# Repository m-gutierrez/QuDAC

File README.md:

# QuDAC

***TODO
+	Update performance measurements
+	include pin-out maps
+	link to ion trap theory, for voltage requirement definitions. 
+	include BOM
+	include assembly photos

This is a 12-channel 20-bit, +/-10V (+/-20V optional) 2MSPS DAC board designed for the Quanta rack system (QuACK). The card was designed to meet the system requirements described bellow while also being simple to populate and interface with the Quanta ion trap system vacuum chamber. Since we assemble these by-hand, we desired as few components as possible while still meeting the requirements of precision experiments with trapped ions. All components should be standard and easy to source, and if possible relatively cheap. A huge exception to the cheap criterion was the use of the ad5791 DAC chip, however there is a a slightly cheaper 18-bit ad5781 which is a drop-in replacement, and a significantly cheaper 16-bit version which requires modification for the different package size.

We've tested the cards at +/-10V, and have achieved reliable update rates at 2MSPS (above the 1.33MSPS datasheet spec for ad5791). Output slew's of ~50V/us have been measured on voltage swings >1V. Noise output is DAC-code dependent, currently limited by the reference-noise (~100nV/sqrt(Hz)). Which We've improved by using an adapter reference board with heavy filtering, 3-pole 1.5Hz cut-off RC filter with capacitors in a bootstrap configuration to minimize offset errors, which reduces the white-noise level to that dominated by the DAC and output op-amp of ~10-20nV/sqrt(Hz) white noise beyond 1kHz.

## Layout 

The board contains 6-layers. This was mostly due to a panel order with other designs requiring 6 layers. The board could easily be re-drawn with 4 layers.
The current layout is 

+	layer 1 - analog signals (top)
+	layer 2 - ground plane
+	layer 3 - analog signals
+	layer 4 - power planes
+	layer 5 - ground plane
+	layer 6 - digital signals (bot)

## component choice

The components where chosen to meet the system requirements, here is a list of the key QuDAC components with a list of the relevant performance spec's.

+	AD5791: DAC, 20-bit, +/-15V supply range, NSD <10nV/sqrt(Hz), 1-2MSPS update rate
+	AD8676: op-amp, +/-15V supply range, NSD <10nV/sqrt(Hz), 10MHz GBP
+	AD8620: op-amp, +/-12V supply range, NSD <10nV/sqrt(Hz), 50MHz GBP, <1us settling to 20-bit accuracy
+	See card-buffer for description of backplane interface.

## Application aim 

Trapped ion quantum computing (TIQC) requires dozens of independently controllable voltage sources with low noise (<100nV/sqrt(Hz)), wide-output range (+/-10V) and fast update rates (>1MSPS). These sources should be extend-able while maintaining synchronized updates, and allow for asynchronous clocking. 

### Output range

In the trap for our particular experiment, Sandia's high optical access trap (HOA v2), there are 96 independent control electrodes. With a trapping height ~68micron, an electrode pitch of ~70micron and control electrodes between the RF electrodes the HOA requires voltages of ~1-4V for trapping potentials producing secular frequencies $\omega_{sec} \approx 2\pi 1MHz$. And allows for +/-20V without damage to the on-chip RF-shunting capacitors. 

### Precision

### Noise level

For room temperature traps typical electric field noise at the ion, due to yet-unknown surface effects, is around ($S_{\nu} \approx 10 \mu V /m\sqrt{Hz}$), which corresponds to an electrode-voltage noise of (~100nV/sqrt(Hz)). Electric field noise in ion traps is a major concern for high fidelity operations, as current two-qubit gate mechanisms use the ions motional state and are first order sensitive to changes in the motional state during the gate operation. In order for gate fidelities to reach error correcting thresholds of ~1e-4 control-voltage noise must be kept well bellow this value. 

### Update rates

Control potentials used in TIQC is typically a compromise between many different concerns. One such concern is that the electric field noise spectrum typical goes as ~1/f such that increasing the secular frequencies is one way to reduce the error due to motional heating of the ion. Another is trap stability and overall trapping depth, since the axial-potential can easily over-take the radial psuedo-potential and reduce the trapping depth to zero. For the trapping dimensions typical used (heights of 50-150micron) useful compromises tend to be between 1-2MHz axial secular frequencies. 

This sets the time scale how changes to control voltages will affect the ions motion, i.e. the time scale for changes to be adiabatic or diabatic. We would like voltage updates to be on the order of or faster than the characteristic ion motion, so update rates exceeding 1MSPS and slew rates >1V/MHz are necessary to meet this constraint. 

### synchronized updates and clocking
The density of the DAC's per card and the clocking rate. where chosen to meet more general back-plane specifications, which takes into account additional devices of interest, clocking speeds, types of isolation achievable over various clock speeds and bus-size. In the end, a 36-bit backplane bus allows for 12-DAC's with independent sync,clock and data lines. In addition to these 36-bits there are an additional 8-bits which by-pass the card select buffers on the backplane interface, which we connect the DAC update pin (LDAC) to allowing multiple cards to be updated simultaneously. 

# Adapters 

There are 3 adapter cards used in our setup. Which assist in converting the card channels into the experiments two DB-50 connectors. 

## Combine2Cards
The first `Combine2Cards' allows us to combine two of the QuDAC cards into a single 24 channel output. The card can be placed directly on the cards within the rack, designed for accommodate the 7HP spacing of the QuACK system. The pin-out is made such that each control voltage is routed as a twisted pair with a ground wire using standard db50 cables. 

## 24CH-2x24CH
The second card, '24CH-2x24CH', copies one 24 channel output into 2 identical pin-out 24-channel outputs. Allowing 48 DAC's to control all 96 trap control voltages. The card also has a 3rd copy for probing voltage outputs.

## filterboard
The final card, 'filterboard', takes two 24-channel inputs and routes them into a single db50-connector. The board also contains 48 7-pole (or 3-pole) coilcraft.com LC filters. In our setup, these are 7-pole 300kHz LC-filters, providing 80db suppression at 1-2MHz. This board is intended to plug directly into the vacuum chamber experiment flange, which routes 100 control signals into the trap-chip through two DB-50 connectors. One of thees boards should also be configured with the resonator-line populated. On our setup, this line consists of a hand-wound ~500nH inductor, connecting to ~20pF trap capacitance producing a ~50MHz resonant frequency, and ~300pF of matching capacitance. The RF tap, consists of a high-voltage 0.2pF capacitor and a 100pF capacitor for a ~1/500 sampling voltage gain. 

# System performance

## range, offset and non-linearity

## noise spectral density

## update rate, slew rate, tone-purity

## synchronous update, clock noise

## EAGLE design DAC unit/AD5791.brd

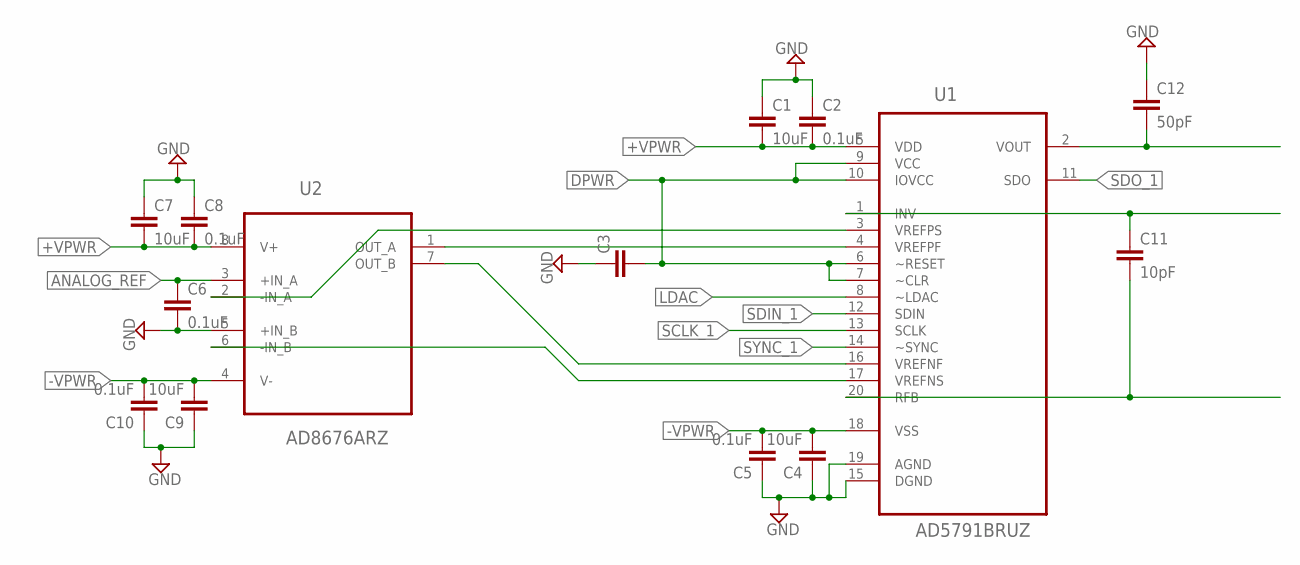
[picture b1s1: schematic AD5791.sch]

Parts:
C1, C4, C7, C9: 10uF; C0805
C2, C5, C6, C8, C10: 0.1uF; C0603
C3: CC0603; C0603
C11: 10pF; C0603
C12: 50pF; C0603
U1: AD5791BRUZ; SOP65P640X120-20N
U2: AD8676ARZ; SOIC127P600X175-8N

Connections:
+VPWR: C1.2, C2.2, C7.2, C8.2, U1.5 (VDD), U2.8 (V+)
-VPWR: C4.2, C5.2, C9.2, C10.2, U1.18 (VSS), U2.4 (V-)
ANALOG_REF: C6.1, U2.3 (+IN_A)
DPWR: C3.2, U1.6 (~RESET), U1.7 (~CLR), U1.9 (VCC), U1.10 (IOVCC)
GND: C1.1, C2.1, C3.1, C4.1, C5.1, C6.2, C7.1, C8.1, C9.1, C10.1, C12.1, U1.15 (DGND), U1.19 (AGND), U2.5 (+IN_B)
LDAC: U1.8 (~LDAC)
unnamed: U1.4 (VREFPF), U2.1 (OUT_A)
unnamed: U1.16 (VREFNF), U2.7 (OUT_B)
unnamed: U1.3 (VREFPS), U2.2 (-IN_A)
unnamed: U1.17 (VREFNS), U2.6 (-IN_B)
unnamed: C12.2, U1.2 (VOUT)
unnamed: C11.1, U1.1 (INV)
unnamed: C11.2, U1.20 (RFB)
SCLK_1: U1.13 (SCLK)
SDIN_1: U1.12 (SDIN)
SDO_1: U1.11 (SDO)
SYNC_1: U1.14 (~SYNC)

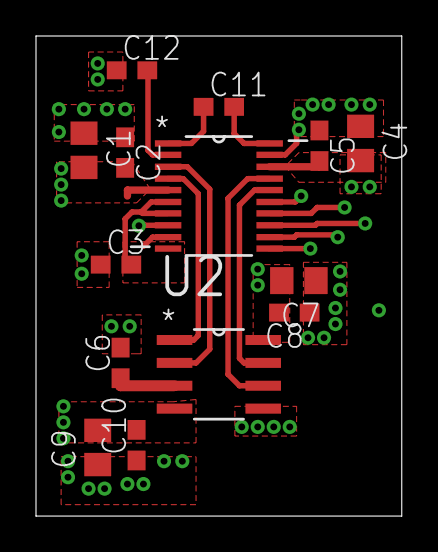
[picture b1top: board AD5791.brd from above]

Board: 4 copper layers, 20.3 x 26.7 mm, 14 parts (0 on the bottom side), 12 nets.

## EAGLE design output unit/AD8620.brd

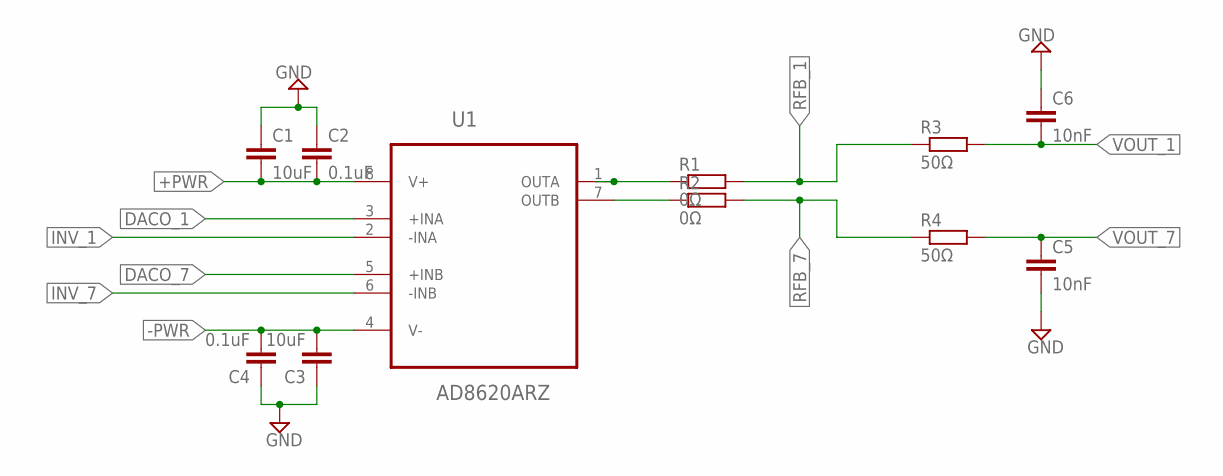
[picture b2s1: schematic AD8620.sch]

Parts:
C1, C3: 10uF; C0805
C2, C4: 0.1uF; C0603
C5, C6: 10nF; C0603
R1, R2: 0Ω; R0603
R3, R4: 50Ω; R0603
U1: AD8620ARZ; SOIC127P600X175-8N

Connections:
+PWR: C1.2, C2.2, U1.8 (V+)
-PWR: C3.2, C4.2, U1.4 (V-)
DACO_1: U1.3 (+INA)
DACO_7: U1.5 (+INB)
GND: C1.1, C2.1, C3.1, C4.1, C5.2, C6.1
INV_1: U1.2 (-INA)
INV_7: U1.6 (-INB)
unnamed: R1.1, U1.1 (OUTA)
unnamed: R2.1, U1.7 (OUTB)
RFB_1: R1.2, R3.1
RFB_7: R2.2, R4.1
VOUT_1: C6.2, R3.2
VOUT_7: C5.1, R4.2

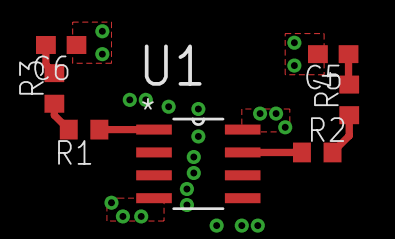
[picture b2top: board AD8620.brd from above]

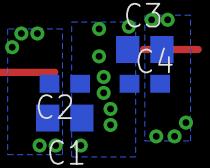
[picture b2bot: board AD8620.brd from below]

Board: 6 copper layers, 11 parts (4 on the bottom side), 9 nets.

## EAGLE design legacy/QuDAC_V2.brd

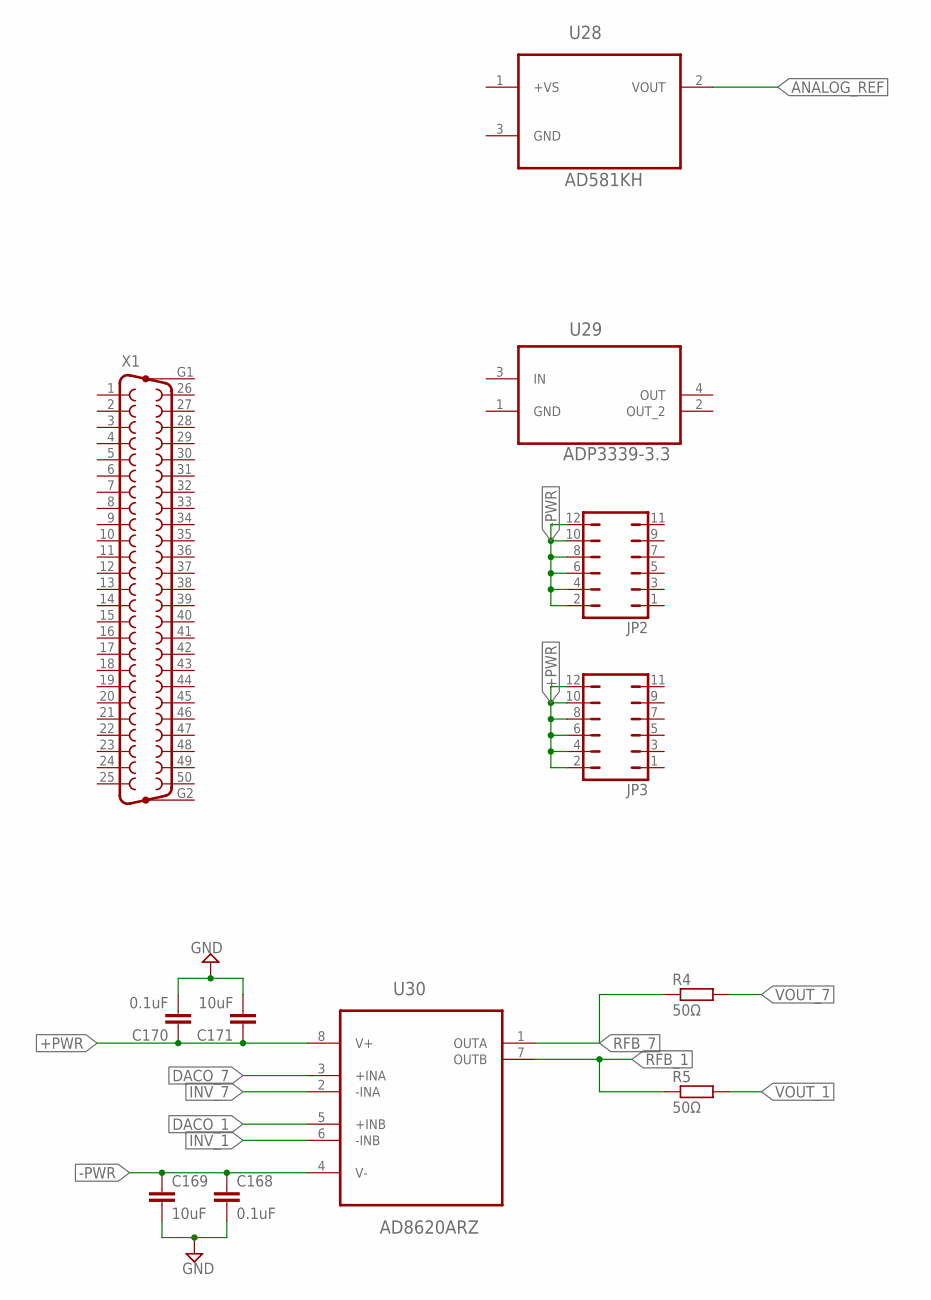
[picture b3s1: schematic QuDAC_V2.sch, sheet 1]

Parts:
C168, C170: 0.1uF; C0603
C169, C171: 10uF; C0805
JP2, JP3: JP6Q
R4, R5: 50Ω; R0603
U28: AD581KH; TO254P939X470-3P
U29: ADP3339-3.3; SOT230P700X180-4N
U30: AD8620ARZ; SOIC127P600X175-8N
X1: F50HP

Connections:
+PWR: C170.1, C171.1, JP3.2, JP3.4, JP3.6, JP3.8, JP3.10, JP3.12, U30.8 (V+)
+VS: U28.1 (+VS)
-PWR: C168.1, C169.1, JP2.2, JP2.4, JP2.6, JP2.8, JP2.10, JP2.12, U30.4 (V-)
ANALOG_REF: U28.2 (VOUT); also elsewhere on the board
DACO_1: U30.5 (+INB); also elsewhere on the board
DACO_7: U30.3 (+INA); also elsewhere on the board
GND: C168.2, C169.2, C170.2, C171.2; also elsewhere on the board
INV_1: U30.6 (-INB); also elsewhere on the board
INV_7: U30.2 (-INA); also elsewhere on the board
RFB_1: R5.1, U30.7 (OUTB); also elsewhere on the board
RFB_7: R4.1, U30.1 (OUTA); also elsewhere on the board
VOUT_1: R5.2
VOUT_7: R4.2

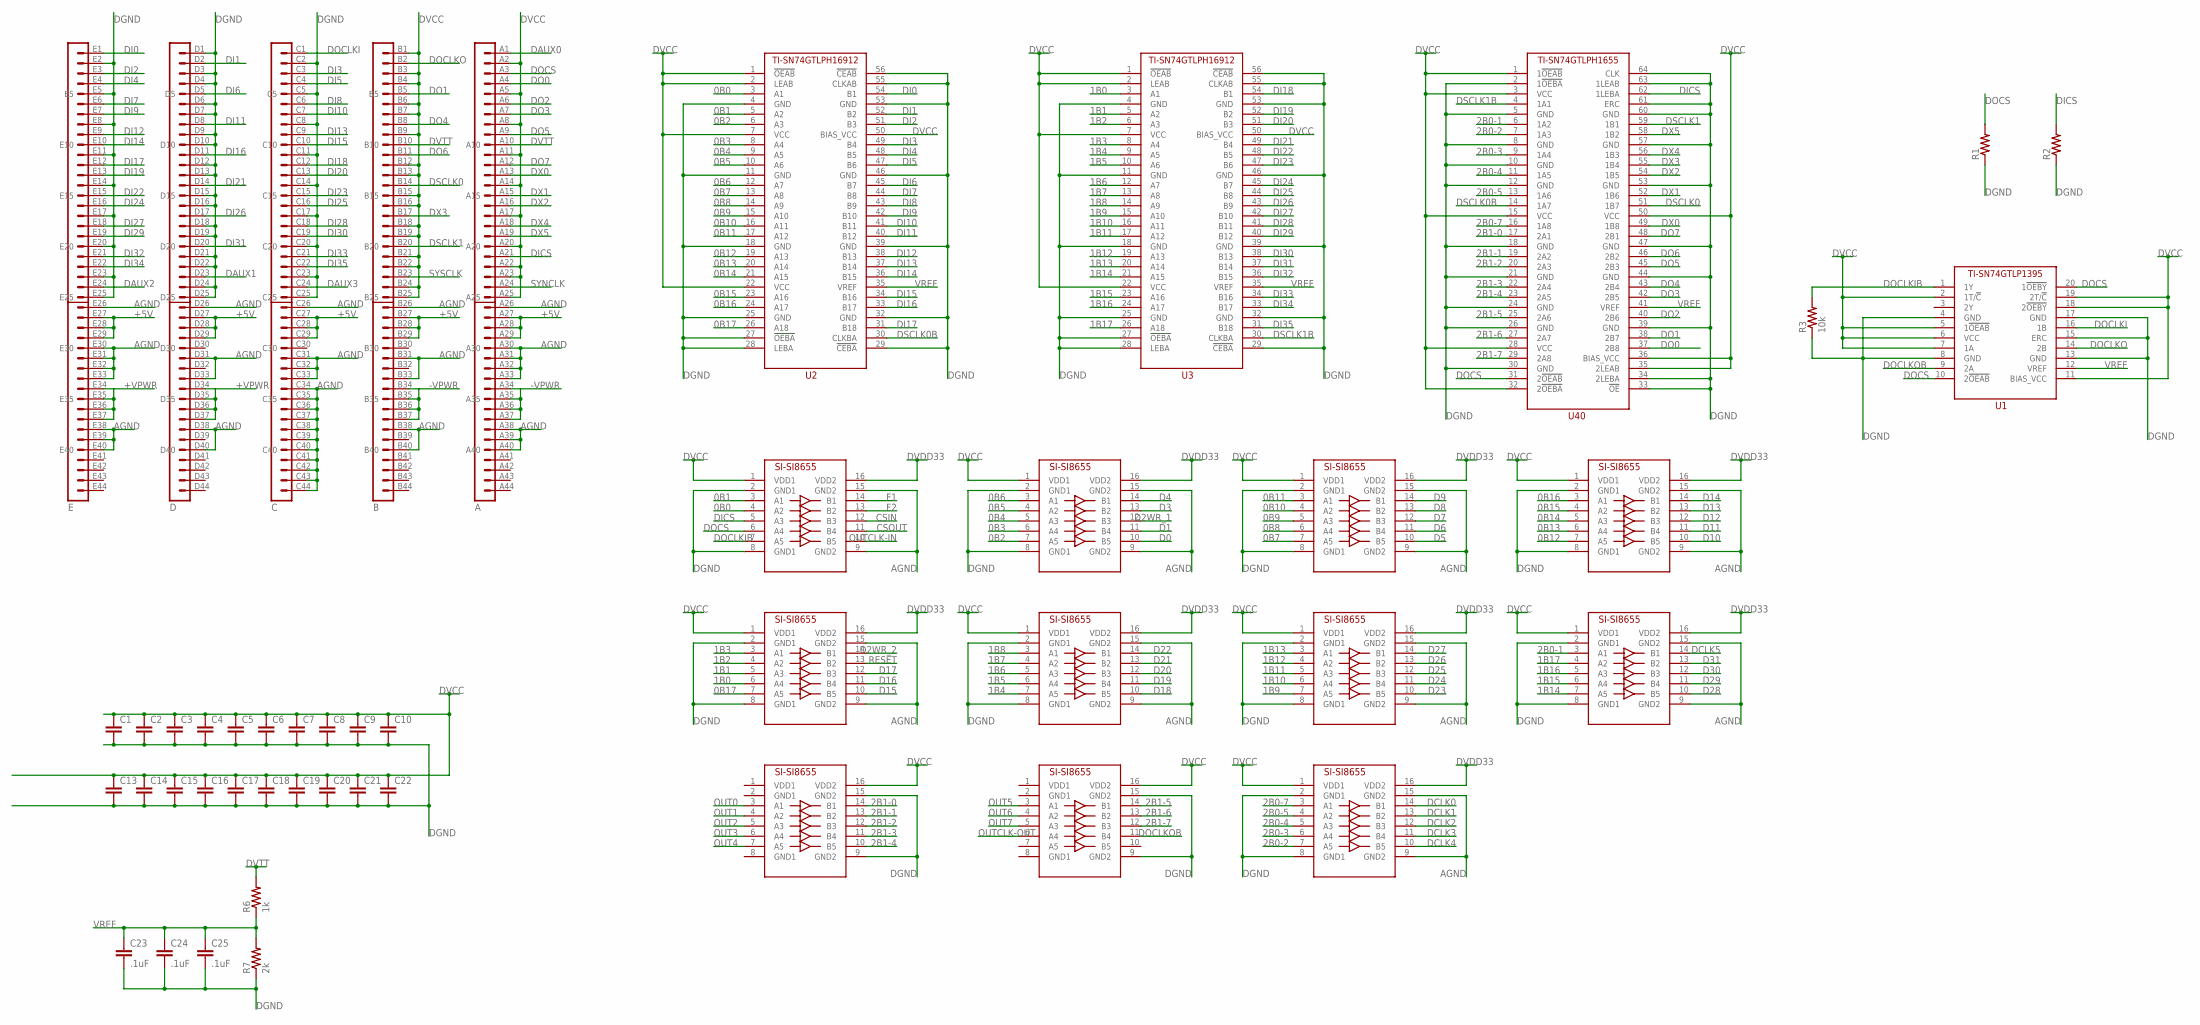
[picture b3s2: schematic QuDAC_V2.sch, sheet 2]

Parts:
C1, C2, C3, C4, C5, C6, C7, C8, C9, C10, C13, C14, C15, C16, C17, C18, C19, C20, C21, C22: CC0603; C0603
C23, C24, C25: .1uF; C0603
ISO1, ISO2, ISO3, ISO4, ISO5, ISO6, ISO7, ISO8, ISO9, ISO10, ISO11: SI-SI8655; QSOP-16
J1: EUROCARD-CPCI-220EUROCARD-B19+AB25-NOFRONTDIM; EUROCARD-CPCI-B19+1B25-NOFRONTDIM
R1, R2: R-US_R0603; R0603
R3: 10k; R0603
R6: 1k; R0805
R7: 2k; R0805
U1: TI-SN74GTLP1395; TSSOP-20
U2, U3: TI-SN74GTLPH16912; TSSOP-56
U40: TI-SN74GTLPH1655; TSSOP-64

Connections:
0B0: ISO1.4 (A2), U2.3 (A1)
0B1: ISO1.3 (A1), U2.5 (A2)
0B2: ISO2.7 (A5), U2.6 (A3)
0B3: ISO2.6 (A4), U2.8 (A4)
0B4: ISO2.5 (A3), U2.9 (A5)
0B5: ISO2.4 (A2), U2.10 (A6)
0B6: ISO2.3 (A1), U2.12 (A7)
0B7: ISO3.7 (A5), U2.13 (A8)
0B8: ISO3.6 (A4), U2.14 (A9)
0B9: ISO3.5 (A3), U2.15 (A10)
0B10: ISO3.4 (A2), U2.16 (A11)
0B11: ISO3.3 (A1), U2.17 (A12)
0B12: ISO4.7 (A5), U2.19 (A13)
0B13: ISO4.6 (A4), U2.20 (A14)
0B14: ISO4.5 (A3), U2.21 (A15)
0B15: ISO4.4 (A2), U2.23 (A16)
0B16: ISO4.3 (A1), U2.24 (A17)
0B17: ISO5.7 (A5), U2.26 (A18)
1B0: ISO5.6 (A4), U3.3 (A1)
1B1: ISO5.5 (A3), U3.5 (A2)
1B2: ISO5.4 (A2), U3.6 (A3)
1B3: ISO5.3 (A1), U3.8 (A4)
1B4: ISO6.7 (A5), U3.9 (A5)
1B5: ISO6.6 (A4), U3.10 (A6)
1B6: ISO6.5 (A3), U3.12 (A7)
1B7: ISO6.4 (A2), U3.13 (A8)
1B8: ISO6.3 (A1), U3.14 (A9)
1B9: ISO7.7 (A5), U3.15 (A10)
1B10: ISO7.6 (A4), U3.16 (A11)
1B11: ISO7.5 (A3), U3.17 (A12)
1B12: ISO7.4 (A2), U3.19 (A13)
1B13: ISO7.3 (A1), U3.20 (A14)
1B14: ISO8.7 (A5), U3.21 (A15)
1B15: ISO8.6 (A4), U3.23 (A16)
1B16: ISO8.5 (A3), U3.24 (A17)
1B17: ISO8.4 (A2), U3.26 (A18)
2B0-1: ISO8.3 (A1), U40.6 (1A2)
2B0-2: ISO11.7 (A5), U40.7 (1A3)
2B0-3: ISO11.6 (A4), U40.9 (1A4)
2B0-4: ISO11.5 (A3), U40.11 (1A5)
2B0-5: ISO11.4 (A2), U40.13 (1A6)
2B0-7: ISO11.3 (A1), U40.16 (1A8)
2B1-0: ISO9.14 (B1), U40.17 (2A1)
2B1-1: ISO9.13 (B2), U40.19 (2A2)
2B1-2: ISO9.12 (B3), U40.20 (2A3)
2B1-3: ISO9.11 (B4), U40.22 (2A4)
2B1-4: ISO9.10 (B5), U40.23 (2A5)
2B1-5: ISO10.14 (B1), U40.25 (2A6)
2B1-6: ISO10.13 (B2), U40.27 (2A7)
2B1-7: ISO10.12 (B3), U40.29 (2A8)
+5V: J1.A27, J1.A28, J1.A29, J1.B27, J1.B28, J1.B29, J1.C27, J1.C28, J1.C29, J1.D27, J1.D28, J1.D29, J1.E27, J1.E28, J1.E29
+VPWR: J1.D34, J1.D35, J1.D36, J1.D37, J1.E34, J1.E35, J1.E36, J1.E37; also elsewhere on the board
-VPWR: J1.A34, J1.A35, J1.A36, J1.A37, J1.B34, J1.B35, J1.B36, J1.B37; also elsewhere on the board
AGND: ISO1.9 (GND2), ISO1.15 (GND2), ISO2.9 (GND2), ISO2.15 (GND2), ISO3.9 (GND2), ISO3.15 (GND2), ISO4.9 (GND2), ISO4.15 (GND2), ISO5.9 (GND2), ISO5.15 (GND2), ISO6.9 (GND2), ISO6.15 (GND2), ISO7.9 (GND2), ISO7.15 (GND2), ISO8.9 (GND2), ISO8.15 (GND2), ISO11.9 (GND2), ISO11.15 (GND2), J1.A26, J1.A30, J1.A31, J1.A32, J1.A33, J1.A38, J1.A39, J1.A40, J1.B26, J1.B31, J1.B33, J1.B38, J1.B40, J1.C26, J1.C31, J1.C32, J1.C33, J1.C34, J1.C35, J1.C36, J1.C37, J1.C38, J1.C39, J1.C40, J1.C41, J1.C42, J1.C43, J1.C44, J1.D26, J1.D31, J1.D33, J1.D38, J1.D40, J1.E26, J1.E30, J1.E31, J1.E32, J1.E33, J1.E38, J1.E39, J1.E40
CSIN: ISO1.12 (B3)
CSOUT: ISO1.11 (B4)
D0: ISO2.10 (B5)
D1: ISO2.11 (B4)
D2WR_1: ISO2.12 (B3)
D2WR_2: ISO5.14 (B1)
D3: ISO2.13 (B2)
D4: ISO2.14 (B1)
D5: ISO3.10 (B5)
D6: ISO3.11 (B4)
D7: ISO3.12 (B3)
D8: ISO3.13 (B2)
D9: ISO3.14 (B1)
D10: ISO4.10 (B5)
D11: ISO4.11 (B4)
D12: ISO4.12 (B3)
D13: ISO4.13 (B2)
D14: ISO4.14 (B1)
D15: ISO5.10 (B5)
D16: ISO5.11 (B4)
D17: ISO5.12 (B3)
D18: ISO6.10 (B5)
D19: ISO6.11 (B4)
D20: ISO6.12 (B3)
D21: ISO6.13 (B2)
D22: ISO6.14 (B1)
D23: ISO7.10 (B5)
D24: ISO7.11 (B4)
D25: ISO7.12 (B3)
D26: ISO7.13 (B2)
D27: ISO7.14 (B1)
D28: ISO8.10 (B5)
D29: ISO8.11 (B4)
D30: ISO8.12 (B3)
D31: ISO8.13 (B2)
DAUX0: J1.A1
DAUX1: J1.D23
DAUX2: J1.E24
DAUX3: J1.C24
DCLK0: ISO11.14 (B1)
DCLK1: ISO11.13 (B2)
DCLK2: ISO11.12 (B3)
DCLK3: ISO11.11 (B4)
DCLK4: ISO11.10 (B5)
DCLK5: ISO8.14 (B1)
DGND: C1.2, C2.2, C3.2, C4.2, C5.2, C6.2, C7.2, C8.2, C9.2, C10.2, C13.2, C14.2, C15.2, C16.2, C17.2, C18.2, C19.2, C20.2, C21.2, C22.2, C23.2, C24.2, C25.2, ISO1.2 (GND1), ISO1.8 (GND1), ISO2.2 (GND1), ISO2.8 (GND1), ISO3.2 (GND1), ISO3.8 (GND1), ISO4.2 (GND1), ISO4.8 (GND1), ISO5.2 (GND1), ISO5.8 (GND1), ISO6.2 (GND1), ISO6.8 (GND1), ISO7.2 (GND1), ISO7.8 (GND1), ISO8.2 (GND1), ISO8.8 (GND1), ISO9.9 (GND2), ISO9.15 (GND2), ISO10.9 (GND2), ISO10.15 (GND2), ISO11.2 (GND1), ISO11.8 (GND1), J1.C2, J1.C5, J1.C8, J1.C11, J1.C14, J1.C17, J1.C20, J1.C23, J1.C25, J1.D1, J1.D3, J1.D4, J1.D6, J1.D7, J1.D9, J1.D10, J1.D12, J1.D13, J1.D15, J1.D16, J1.D18, J1.D19, J1.D21, J1.D22, J1.D24, J1.D25, J1.E2, J1.E5, J1.E8, J1.E11, J1.E14, J1.E17, J1.E20, J1.E23, J1.E25, R1.1, R2.1, R3.1, R7.1, U1.4 (GND), U1.8 (GND), U1.13 (GND), U1.15 (ERC), U1.17 (GND), U2.4 (GND), U2.11 (GND), U2.18 (GND), U2.25 (GND), U2.27 (!OEBA), U2.28 (LEBA), U2.29 (!CEBA), U2.32 (GND), U2.39 (GND), U2.46 (GND), U2.53 (GND), U2.55 (CLKAB), U2.56 (!CEAB), U3.4 (GND), U3.11 (GND), U3.18 (GND), U3.25 (GND), U3.27 (!OEBA), U3.28 (LEBA), U3.29 (!CEBA), U3.32 (GND), U3.39 (GND), U3.46 (GND), U3.53 (GND), U3.55 (CLKAB), U3.56 (!CEAB), U40.2 (1!OEBA), U40.5 (GND), U40.8 (GND), U40.10 (GND), U40.12 (GND), U40.18 (GND), U40.21 (GND), U40.24 (GND), U40.26 (GND), U40.30 (GND), U40.33 (!OE), U40.34 (2LEBA), U40.39 (GND), U40.44 (GND), U40.47 (GND), U40.53 (GND), U40.57 (GND), U40.60 (GND), U40.61 (ERC), U40.63 (1LEAB), U40.64 (CLK)
DI0: J1.E1, U2.54 (B1)
DI1: J1.D2, U2.52 (B2)
DI2: J1.E3, U2.51 (B3)
DI3: J1.C3, U2.49 (B4)
DI4: J1.E4, U2.48 (B5)
DI5: J1.C4, U2.47 (B6)
DI6: J1.D5, U2.45 (B7)
DI7: J1.E6, U2.44 (B8)
DI8: J1.C6, U2.43 (B9)
DI9: J1.E7, U2.42 (B10)
DI10: J1.C7, U2.41 (B11)
DI11: J1.D8, U2.40 (B12)
DI12: J1.E9, U2.38 (B13)
DI13: J1.C9, U2.37 (B14)
DI14: J1.E10, U2.36 (B15)
DI15: J1.C10, U2.34 (B16)
DI16: J1.D11, U2.33 (B17)
DI17: J1.E12, U2.31 (B18)
DI18: J1.C12, U3.54 (B1)
DI19: J1.E13, U3.52 (B2)
DI20: J1.C13, U3.51 (B3)
DI21: J1.D14, U3.49 (B4)
DI22: J1.E15, U3.48 (B5)
DI23: J1.C15, U3.47 (B6)
DI24: J1.E16, U3.45 (B7)
DI25: J1.C16, U3.44 (B8)
DI26: J1.D17, U3.43 (B9)
DI27: J1.E18, U3.42 (B10)
DI28: J1.C18, U3.41 (B11)
DI29: J1.E19, U3.40 (B12)
DI30: J1.C19, U3.38 (B13)
DI31: J1.D20, U3.37 (B14)
DI32: J1.E21, U3.36 (B15)
DI33: J1.C21, U3.34 (B16)
DI34: J1.E22, U3.33 (B17)
DI35: J1.C22, U3.31 (B18)
DICS: ISO1.5 (A3), J1.A21, R2.2, U40.62 (1LEBA)
DO0: J1.A4, U40.37 (2B8)
DO1: J1.B5, U40.38 (2B7)
DO2: J1.A6, U40.40 (2B6)
DO3: J1.A7, U40.42 (2B5)
DO4: J1.B8, U40.43 (2B4)
DO5: J1.A9, U40.45 (2B3)
DO6: J1.B11, U40.46 (2B2)
DO7: J1.A12, U40.48 (2B1)
DOCLKI: J1.C1, U1.16 (1B)
DOCLKIB: ISO1.7 (A5), R3.2, U1.1 (1Y)
DOCLKO: J1.B2, U1.14 (2B)
DOCLKOB: ISO10.11 (B4), U1.9 (2A)
DOCS: ISO1.6 (A4), J1.A3, R1.2, U1.10 (2!OEAB), U1.20 (1!OEBY), U40.31 (2!OEAB)
DSCLK0: J1.B14, U40.51 (1B7)
DSCLK0B: U2.30 (CLKBA), U40.14 (1A7)
DSCLK1: J1.B20, U40.59 (1B1)
DSCLK1B: U3.30 (CLKBA), U40.4 (1A1)
DVCC: C1.1, C2.1, C3.1, C4.1, C5.1, C6.1, C7.1, C8.1, C9.1, C10.1, C13.1, C14.1, C15.1, C16.1, C17.1, C18.1, C19.1, C20.1, C21.1, C22.1, ISO1.1 (VDD1), ISO2.1 (VDD1), ISO3.1 (VDD1), ISO4.1 (VDD1), ISO5.1 (VDD1), ISO6.1 (VDD1), ISO7.1 (VDD1), ISO8.1 (VDD1), ISO9.16 (VDD2), ISO10.16 (VDD2), ISO11.1 (VDD1), J1.A2, J1.A5, J1.A8, J1.A11, J1.A14, J1.A17, J1.A20, J1.A22, J1.A23, J1.A25, J1.B1, J1.B3, J1.B4, J1.B6, J1.B7, J1.B9, J1.B12, J1.B13, J1.B15, J1.B16, J1.B18, J1.B19, J1.B21, J1.B22, J1.B24, J1.B25, U1.2 (1T/!C), U1.5 (1!OEAB), U1.6 (VCC), U1.7 (1A), U1.11 (BIAS_VCC), U1.18 (2!OEBY), U1.19 (2T/!C), U2.1 (!OEAB), U2.2 (LEAB), U2.7 (VCC), U2.22 (VCC), U2.50 (BIAS_VCC), U3.1 (!OEAB), U3.2 (LEAB), U3.7 (VCC), U3.22 (VCC), U3.50 (BIAS_VCC), U40.1 (1!OEAB), U40.3 (VCC), U40.15 (VCC), U40.28 (VCC), U40.32 (2!OEBA), U40.35 (2LEAB), U40.36 (BIAS_VCC), U40.50 (VCC)
DVDD33: ISO1.16 (VDD2), ISO2.16 (VDD2), ISO3.16 (VDD2), ISO4.16 (VDD2), ISO5.16 (VDD2), ISO6.16 (VDD2), ISO7.16 (VDD2), ISO8.16 (VDD2), ISO11.16 (VDD2)
DVTT: J1.A10, J1.B10, R6.2
DX0: J1.A13, U40.49 (1B8)
DX1: J1.A15, U40.52 (1B6)
DX2: J1.A16, U40.54 (1B5)
DX3: J1.B17, U40.55 (1B4)
DX4: J1.A18, U40.56 (1B3)
DX5: J1.A19, U40.58 (1B2)
F1: ISO1.14 (B1)
F2: ISO1.13 (B2)
OUT0: ISO9.3 (A1)
OUT1: ISO9.4 (A2)
OUT2: ISO9.5 (A3)
OUT3: ISO9.6 (A4)
OUT4: ISO9.7 (A5)
OUT5: ISO10.3 (A1)
OUT6: ISO10.4 (A2)
OUT7: ISO10.5 (A3)
OUTCLK-IN: ISO1.10 (B5)
OUTCLK-OUT: ISO10.6 (A4)
RESET: ISO5.13 (B2)
SYNCLK: J1.A24
SYSCLK: J1.B23
VREF: C23.1, C24.1, C25.1, R6.1, R7.2, U1.12 (VREF), U2.35 (VREF), U3.35 (VREF), U40.41 (VREF)

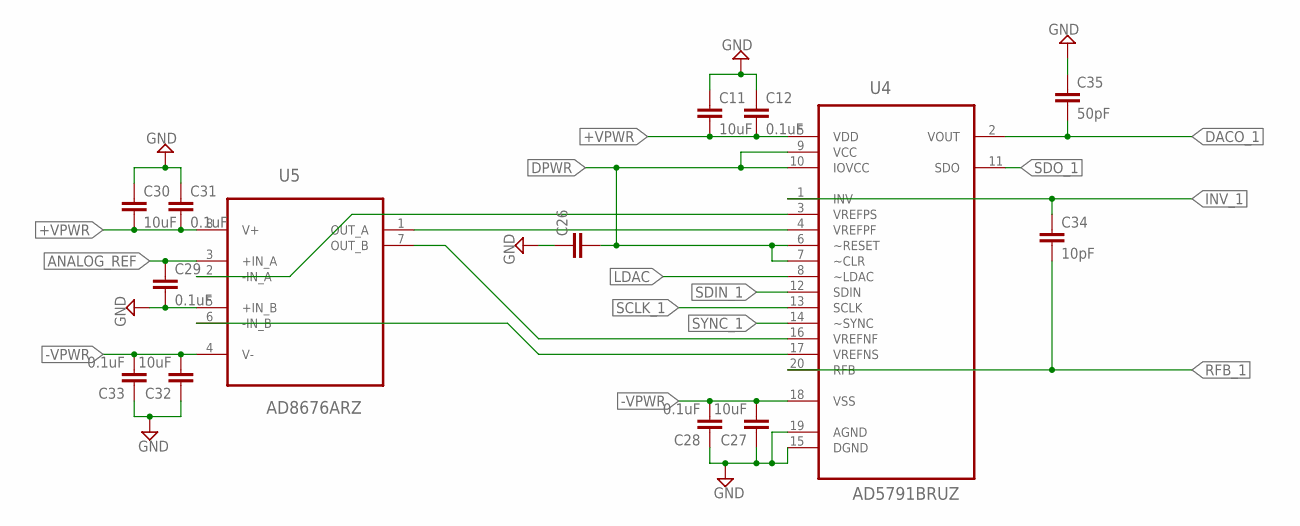
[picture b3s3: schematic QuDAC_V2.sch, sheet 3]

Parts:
C11, C27, C30, C32: 10uF; C0805
C12, C28, C29, C31, C33: 0.1uF; C0603
C26: CC0603; C0603
C34: 10pF; C0603
C35: 50pF; C0603
U4: AD5791BRUZ; SOP65P640X120-20N
U5: AD8676ARZ; SOIC127P600X175-8N

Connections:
+VPWR: C11.2, C12.2, C30.2, C31.2, U4.5 (VDD), U5.8 (V+); also elsewhere on the board
-VPWR: C27.2, C28.2, C32.2, C33.2, U4.18 (VSS), U5.4 (V-); also elsewhere on the board
ANALOG_REF: C29.1, U5.3 (+IN_A); also elsewhere on the board
DACO_1: C35.2, U4.2 (VOUT); also elsewhere on the board
DPWR: C26.2, U4.6 (~RESET), U4.7 (~CLR), U4.9 (VCC), U4.10 (IOVCC); also elsewhere on the board
GND: C11.1, C12.1, C26.1, C27.1, C28.1, C29.2, C30.1, C31.1, C32.1, C33.1, C35.1, U4.15 (DGND), U4.19 (AGND), U5.5 (+IN_B); also elsewhere on the board
INV_1: C34.1, U4.1 (INV); also elsewhere on the board
LDAC: U4.8 (~LDAC); also elsewhere on the board
unnamed: U4.4 (VREFPF), U5.1 (OUT_A)
unnamed: U4.16 (VREFNF), U5.7 (OUT_B)
unnamed: U4.3 (VREFPS), U5.2 (-IN_A)
unnamed: U4.17 (VREFNS), U5.6 (-IN_B)
RFB_1: C34.2, U4.20 (RFB); also elsewhere on the board
SCLK_1: U4.13 (SCLK)
SDIN_1: U4.12 (SDIN)
SDO_1: U4.11 (SDO)
SYNC_1: U4.14 (~SYNC)

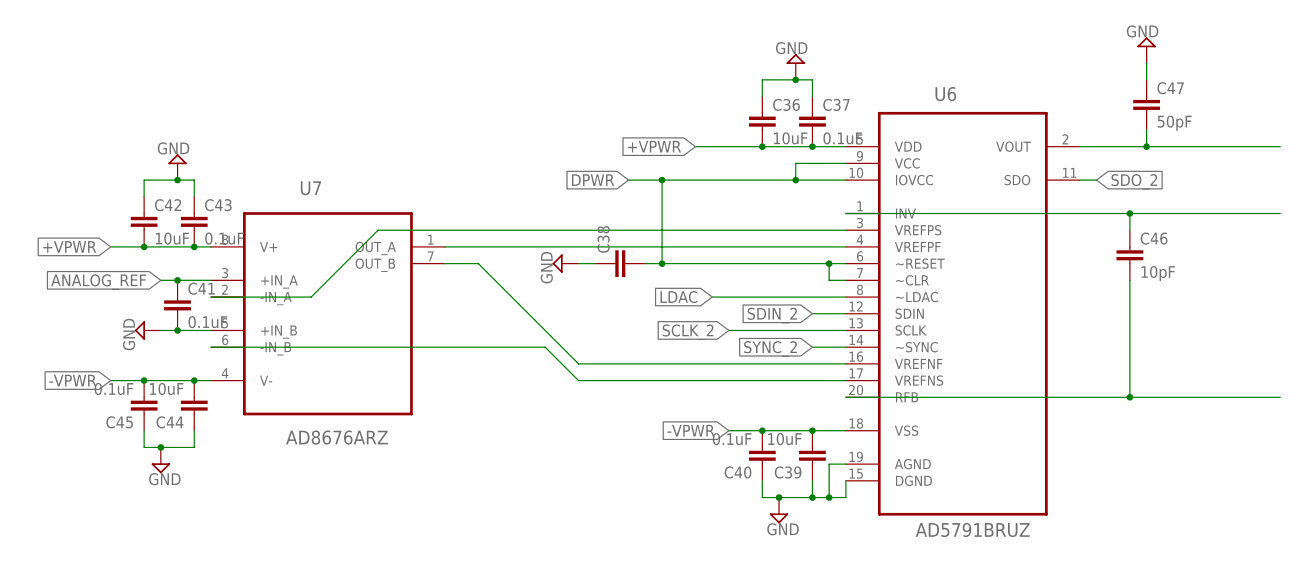
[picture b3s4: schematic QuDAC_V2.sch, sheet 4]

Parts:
C36, C39, C42, C44: 10uF; C0805
C37, C40, C41, C43, C45: 0.1uF; C0603
C38: CC0603; C0603
C46: 10pF; C0603
C47: 50pF; C0603
U6: AD5791BRUZ; SOP65P640X120-20N
U7: AD8676ARZ; SOIC127P600X175-8N

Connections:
+VPWR: C36.2, C37.2, C42.2, C43.2, U6.5 (VDD), U7.8 (V+); also elsewhere on the board
-VPWR: C39.2, C40.2, C44.2, C45.2, U6.18 (VSS), U7.4 (V-); also elsewhere on the board
ANALOG_REF: C41.1, U7.3 (+IN_A); also elsewhere on the board
DPWR: C38.2, U6.6 (~RESET), U6.7 (~CLR), U6.9 (VCC), U6.10 (IOVCC); also elsewhere on the board
GND: C36.1, C37.1, C38.1, C39.1, C40.1, C41.2, C42.1, C43.1, C44.1, C45.1, C47.1, U6.15 (DGND), U6.19 (AGND), U7.5 (+IN_B); also elsewhere on the board
LDAC: U6.8 (~LDAC); also elsewhere on the board
unnamed: U6.4 (VREFPF), U7.1 (OUT_A)
unnamed: U6.16 (VREFNF), U7.7 (OUT_B)
unnamed: U6.3 (VREFPS), U7.2 (-IN_A)
unnamed: U6.17 (VREFNS), U7.6 (-IN_B)
unnamed: C47.2, U6.2 (VOUT)
unnamed: C46.1, U6.1 (INV)
unnamed: C46.2, U6.20 (RFB)
SCLK_2: U6.13 (SCLK)
SDIN_2: U6.12 (SDIN)
SDO_2: U6.11 (SDO)
SYNC_2: U6.14 (~SYNC)

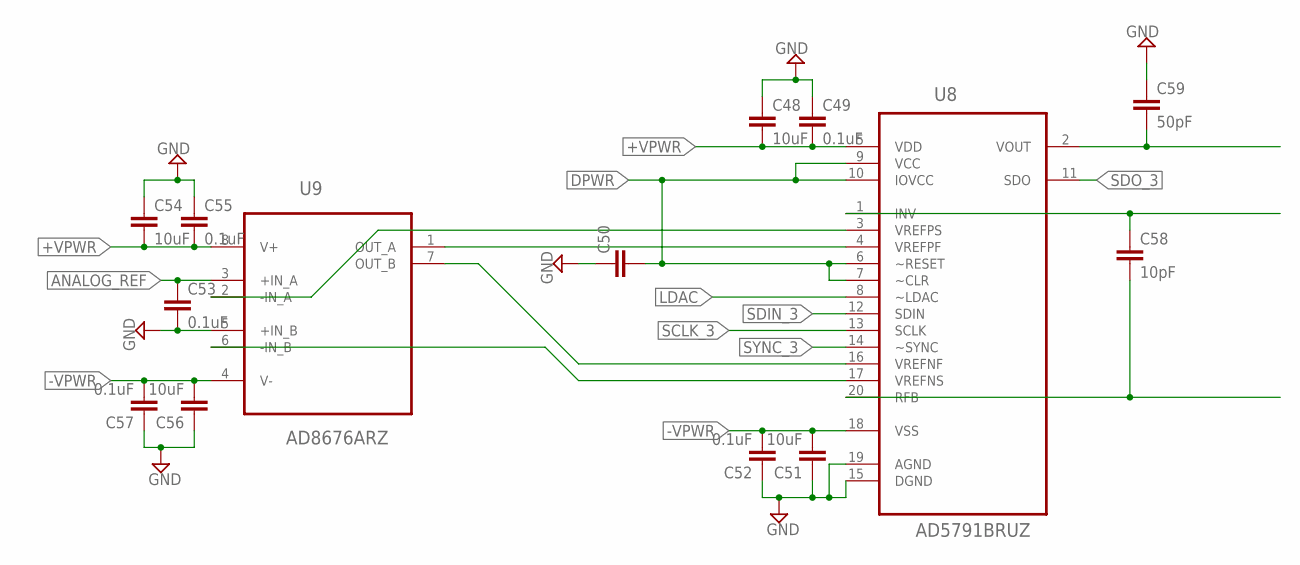
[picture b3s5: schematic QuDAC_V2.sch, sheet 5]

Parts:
C48, C51, C54, C56: 10uF; C0805
C49, C52, C53, C55, C57: 0.1uF; C0603
C50: CC0603; C0603
C58: 10pF; C0603
C59: 50pF; C0603
U8: AD5791BRUZ; SOP65P640X120-20N
U9: AD8676ARZ; SOIC127P600X175-8N

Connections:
+VPWR: C48.2, C49.2, C54.2, C55.2, U8.5 (VDD), U9.8 (V+); also elsewhere on the board
-VPWR: C51.2, C52.2, C56.2, C57.2, U8.18 (VSS), U9.4 (V-); also elsewhere on the board
ANALOG_REF: C53.1, U9.3 (+IN_A); also elsewhere on the board
DPWR: C50.2, U8.6 (~RESET), U8.7 (~CLR), U8.9 (VCC), U8.10 (IOVCC); also elsewhere on the board
GND: C48.1, C49.1, C50.1, C51.1, C52.1, C53.2, C54.1, C55.1, C56.1, C57.1, C59.1, U8.15 (DGND), U8.19 (AGND), U9.5 (+IN_B); also elsewhere on the board
LDAC: U8.8 (~LDAC); also elsewhere on the board
unnamed: U8.4 (VREFPF), U9.1 (OUT_A)
unnamed: U8.16 (VREFNF), U9.7 (OUT_B)
unnamed: U8.3 (VREFPS), U9.2 (-IN_A)
unnamed: U8.17 (VREFNS), U9.6 (-IN_B)
unnamed: C59.2, U8.2 (VOUT)
unnamed: C58.1, U8.1 (INV)
unnamed: C58.2, U8.20 (RFB)
SCLK_3: U8.13 (SCLK)
SDIN_3: U8.12 (SDIN)
SDO_3: U8.11 (SDO)
SYNC_3: U8.14 (~SYNC)

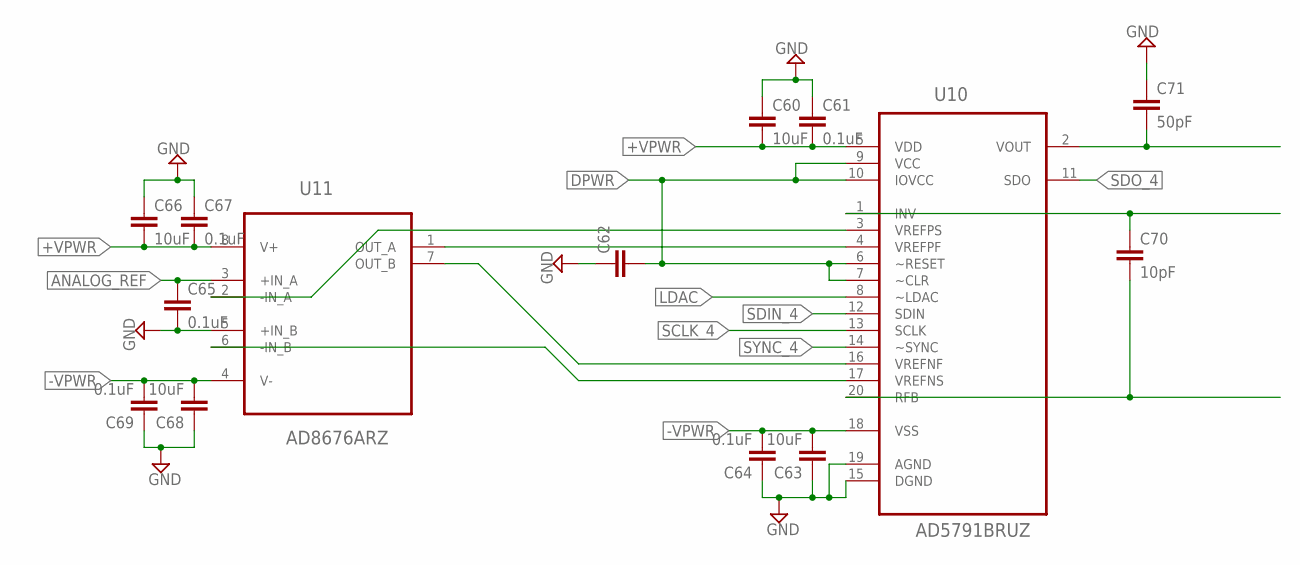
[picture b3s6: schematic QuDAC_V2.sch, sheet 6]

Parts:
C60, C63, C66, C68: 10uF; C0805
C61, C64, C65, C67, C69: 0.1uF; C0603
C62: CC0603; C0603
C70: 10pF; C0603
C71: 50pF; C0603
U10: AD5791BRUZ; SOP65P640X120-20N
U11: AD8676ARZ; SOIC127P600X175-8N

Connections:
+VPWR: C60.2, C61.2, C66.2, C67.2, U10.5 (VDD), U11.8 (V+); also elsewhere on the board
-VPWR: C63.2, C64.2, C68.2, C69.2, U10.18 (VSS), U11.4 (V-); also elsewhere on the board
ANALOG_REF: C65.1, U11.3 (+IN_A); also elsewhere on the board
DPWR: C62.2, U10.6 (~RESET), U10.7 (~CLR), U10.9 (VCC), U10.10 (IOVCC); also elsewhere on the board
GND: C60.1, C61.1, C62.1, C63.1, C64.1, C65.2, C66.1, C67.1, C68.1, C69.1, C71.1, U10.15 (DGND), U10.19 (AGND), U11.5 (+IN_B); also elsewhere on the board
LDAC: U10.8 (~LDAC); also elsewhere on the board
unnamed: U10.4 (VREFPF), U11.1 (OUT_A)
unnamed: U10.16 (VREFNF), U11.7 (OUT_B)
unnamed: U10.3 (VREFPS), U11.2 (-IN_A)
unnamed: U10.17 (VREFNS), U11.6 (-IN_B)
unnamed: C71.2, U10.2 (VOUT)
unnamed: C70.1, U10.1 (INV)
unnamed: C70.2, U10.20 (RFB)
SCLK_4: U10.13 (SCLK)
SDIN_4: U10.12 (SDIN)
SDO_4: U10.11 (SDO)
SYNC_4: U10.14 (~SYNC)

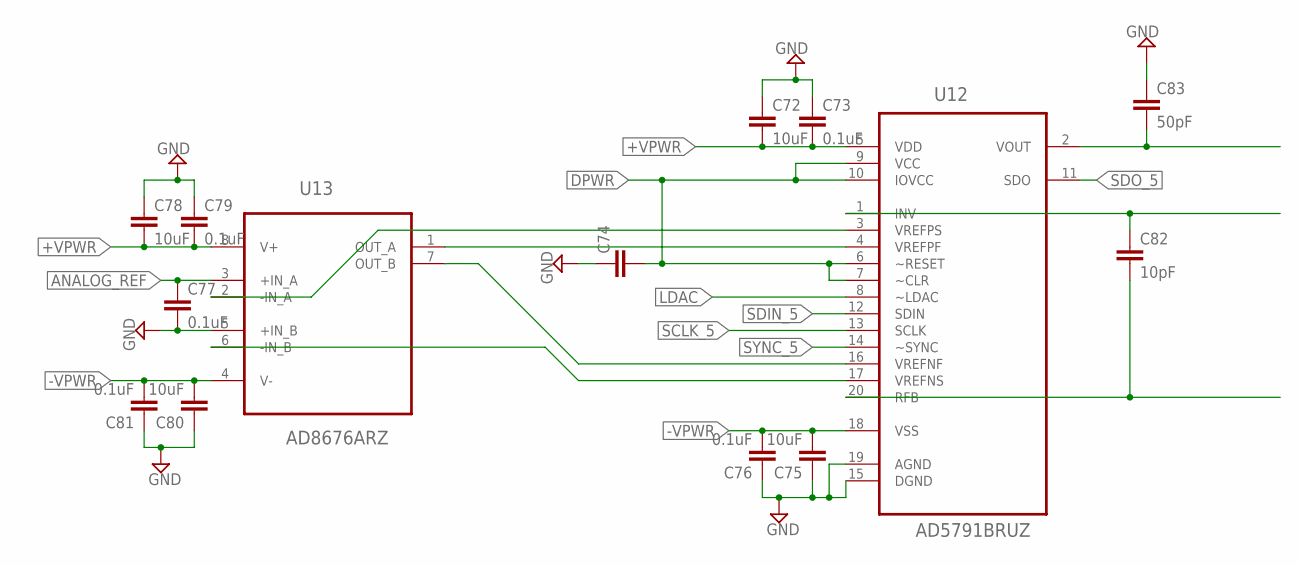
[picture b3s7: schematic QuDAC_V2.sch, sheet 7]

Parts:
C72, C75, C78, C80: 10uF; C0805
C73, C76, C77, C79, C81: 0.1uF; C0603
C74: CC0603; C0603
C82: 10pF; C0603
C83: 50pF; C0603
U12: AD5791BRUZ; SOP65P640X120-20N
U13: AD8676ARZ; SOIC127P600X175-8N

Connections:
+VPWR: C72.2, C73.2, C78.2, C79.2, U12.5 (VDD), U13.8 (V+); also elsewhere on the board
-VPWR: C75.2, C76.2, C80.2, C81.2, U12.18 (VSS), U13.4 (V-); also elsewhere on the board
ANALOG_REF: C77.1, U13.3 (+IN_A); also elsewhere on the board
DPWR: C74.2, U12.6 (~RESET), U12.7 (~CLR), U12.9 (VCC), U12.10 (IOVCC); also elsewhere on the board
GND: C72.1, C73.1, C74.1, C75.1, C76.1, C77.2, C78.1, C79.1, C80.1, C81.1, C83.1, U12.15 (DGND), U12.19 (AGND), U13.5 (+IN_B); also elsewhere on the board
LDAC: U12.8 (~LDAC); also elsewhere on the board
unnamed: U12.4 (VREFPF), U13.1 (OUT_A)
unnamed: U12.16 (VREFNF), U13.7 (OUT_B)
unnamed: U12.3 (VREFPS), U13.2 (-IN_A)
unnamed: U12.17 (VREFNS), U13.6 (-IN_B)
unnamed: C83.2, U12.2 (VOUT)
unnamed: C82.1, U12.1 (INV)
unnamed: C82.2, U12.20 (RFB)
SCLK_5: U12.13 (SCLK)
SDIN_5: U12.12 (SDIN)
SDO_5: U12.11 (SDO)
SYNC_5: U12.14 (~SYNC)

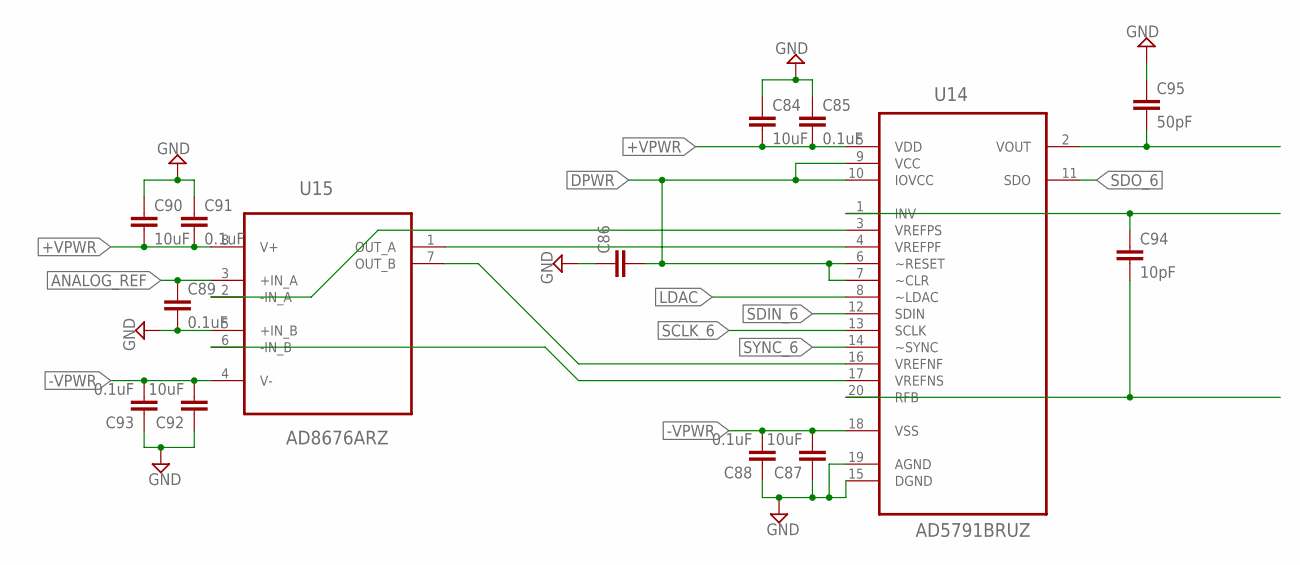
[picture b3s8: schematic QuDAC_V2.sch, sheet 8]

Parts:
C84, C87, C90, C92: 10uF; C0805
C85, C88, C89, C91, C93: 0.1uF; C0603
C86: CC0603; C0603
C94: 10pF; C0603
C95: 50pF; C0603
U14: AD5791BRUZ; SOP65P640X120-20N
U15: AD8676ARZ; SOIC127P600X175-8N

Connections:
+VPWR: C84.2, C85.2, C90.2, C91.2, U14.5 (VDD), U15.8 (V+); also elsewhere on the board
-VPWR: C87.2, C88.2, C92.2, C93.2, U14.18 (VSS), U15.4 (V-); also elsewhere on the board
ANALOG_REF: C89.1, U15.3 (+IN_A); also elsewhere on the board
DPWR: C86.2, U14.6 (~RESET), U14.7 (~CLR), U14.9 (VCC), U14.10 (IOVCC); also elsewhere on the board
GND: C84.1, C85.1, C86.1, C87.1, C88.1, C89.2, C90.1, C91.1, C92.1, C93.1, C95.1, U14.15 (DGND), U14.19 (AGND), U15.5 (+IN_B); also elsewhere on the board
LDAC: U14.8 (~LDAC); also elsewhere on the board
unnamed: U14.4 (VREFPF), U15.1 (OUT_A)
unnamed: U14.16 (VREFNF), U15.7 (OUT_B)
unnamed: U14.3 (VREFPS), U15.2 (-IN_A)
unnamed: U14.17 (VREFNS), U15.6 (-IN_B)
unnamed: C95.2, U14.2 (VOUT)
unnamed: C94.1, U14.1 (INV)
unnamed: C94.2, U14.20 (RFB)
SCLK_6: U14.13 (SCLK)
SDIN_6: U14.12 (SDIN)
SDO_6: U14.11 (SDO)
SYNC_6: U14.14 (~SYNC)

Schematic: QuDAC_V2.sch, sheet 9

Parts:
C96, C99, C102, C104: 10uF; C0805
C97, C100, C101, C103, C105: 0.1uF; C0603
C98: CC0603; C0603
C106: 10pF; C0603
C107: 50pF; C0603
U16: AD5791BRUZ; SOP65P640X120-20N
U17: AD8676ARZ; SOIC127P600X175-8N

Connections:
+VPWR: C96.2, C97.2, C102.2, C103.2, U16.5 (VDD), U17.8 (V+); also elsewhere on the board
-VPWR: C99.2, C100.2, C104.2, C105.2, U16.18 (VSS), U17.4 (V-); also elsewhere on the board
ANALOG_REF: C101.1, U17.3 (+IN_A); also elsewhere on the board
DACO_7: C107.2, U16.2 (VOUT); also elsewhere on the board
DPWR: C98.2, U16.6 (~RESET), U16.7 (~CLR), U16.9 (VCC), U16.10 (IOVCC); also elsewhere on the board
GND: C96.1, C97.1, C98.1, C99.1, C100.1, C101.2, C102.1, C103.1, C104.1, C105.1, C107.1, U16.15 (DGND), U16.19 (AGND), U17.5 (+IN_B); also elsewhere on the board
INV_7: C106.1, U16.1 (INV); also elsewhere on the board
LDAC: U16.8 (~LDAC); also elsewhere on the board
unnamed: U16.4 (VREFPF), U17.1 (OUT_A)
unnamed: U16.16 (VREFNF), U17.7 (OUT_B)
unnamed: U16.3 (VREFPS), U17.2 (-IN_A)
unnamed: U16.17 (VREFNS), U17.6 (-IN_B)
RFB_7: C106.2, U16.20 (RFB); also elsewhere on the board
SCLK_7: U16.13 (SCLK)
SDIN_7: U16.12 (SDIN)
SDO_7: U16.11 (SDO)
SYNC_7: U16.14 (~SYNC)
